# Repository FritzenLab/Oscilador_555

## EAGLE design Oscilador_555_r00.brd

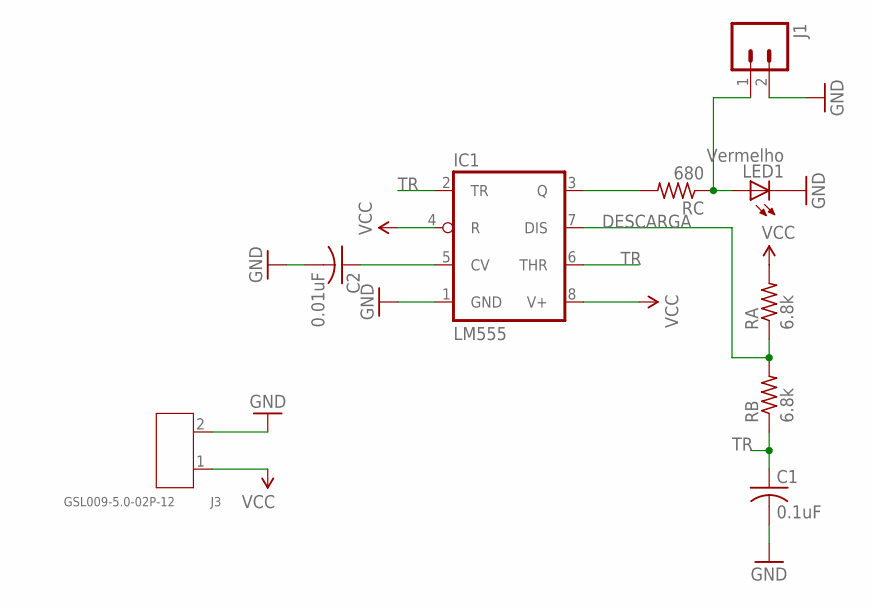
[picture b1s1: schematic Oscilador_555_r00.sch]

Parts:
C1: 0.1uF; C050-024X044
C2: 0.01uF; C050-024X044
IC1: LM555; DIL08-ROUND
J1: M02PTH; 1X02
J3: GSL009-5.0-02P-12; H2-5.0-10.5X8.0MM
LED1: Vermelho; LED5MM
RA: 6.8k; 0207/10
RB: 6.8k; 0207/10
RC: 680; 0207/10

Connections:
DESCARGA: IC1.7 (DIS), RA.1, RB.2
GND: C1.2, C2.2, IC1.1 (GND), J1.2, J3.2, LED1.K (C)
unnamed: C2.1, IC1.5 (CV)
unnamed: J1.1, LED1.A, RC.1
unnamed: IC1.3 (Q), RC.2
TR: C1.1, IC1.2 (TR), IC1.6 (THR), RB.1
VCC: IC1.4 (R), IC1.8 (V+), J3.1, RA.2

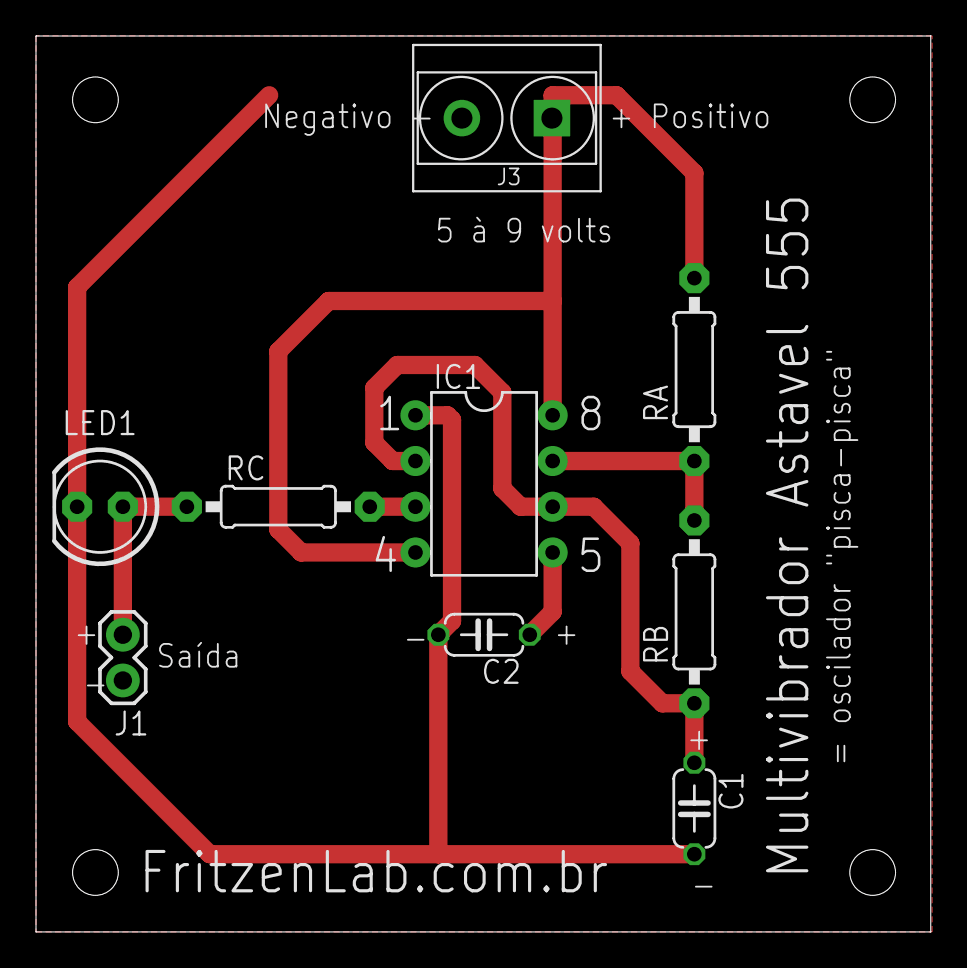
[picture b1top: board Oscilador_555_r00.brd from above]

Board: 2 copper layers, 49.7 x 49.8 mm, 9 parts (0 on the bottom side), 7 nets.

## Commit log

2016-03-02 Lançamento inicial de arquivos
    Arquivos em formato Eagle CADE (esquemático e layout de placa) do
    oscilador (pisca-pisca) educacional utilizando o CI 555
2016-04-01 Primeira revisao e arquivos zip para producao
    Primeira revisão (estética e para adicionar conector KRE 5mm); criado
    Gerber para producao da PCI
2019-02-10 revisado desenho da PCI
    revisado desenho da PCI
2019-02-10 arquivos de fabricacao
    arquivos de fabricacao
2024-11-02 backups
2024-11-03 generated gerbers

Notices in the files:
parts and their libraries:
SparkFun-Connectors: Licensing: Creative Commons ShareAlike 4.0 International - https://creativecommons.org/licenses/by-sa/4.0
